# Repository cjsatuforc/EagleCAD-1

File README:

This repository contains the projects I will be using for learning EagleCAD software

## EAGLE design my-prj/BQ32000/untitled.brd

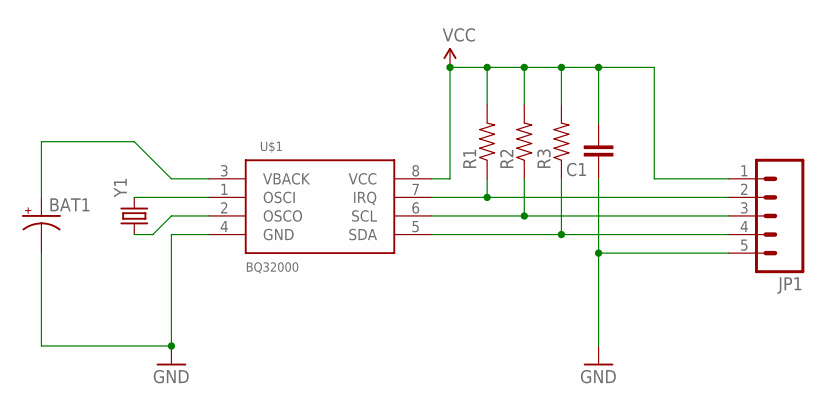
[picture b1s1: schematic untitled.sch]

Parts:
BAT1: CAP_POLPTH3; CPOL-RADIAL-1000UF-63V
C1: CAP0805; 0805
JP1: M05LOCK; 1X05_LOCK
R1, R2, R3: RESISTOR0805-RES; 0805
U$1: BQ32000; SO08
Y1: CRYSTAL32-SMD; CRYSTAL-32KHZ-SMD

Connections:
GND: BAT1.2 (-), C1.1, JP1.5, U$1.4 (GND)
unnamed: BAT1.1 (+), U$1.3 (VBACK)
unnamed: JP1.2, R1.1, U$1.7 (IRQ)
unnamed: JP1.3, R2.1, U$1.6 (SCL)
unnamed: JP1.4, R3.1, U$1.5 (SDA)
unnamed: U$1.1 (OSCI), Y1.X2 (2)
unnamed: U$1.2 (OSCO), Y1.X1 (1)
VCC: C1.2, JP1.1, R1.2, R2.2, R3.2, U$1.8 (VCC)

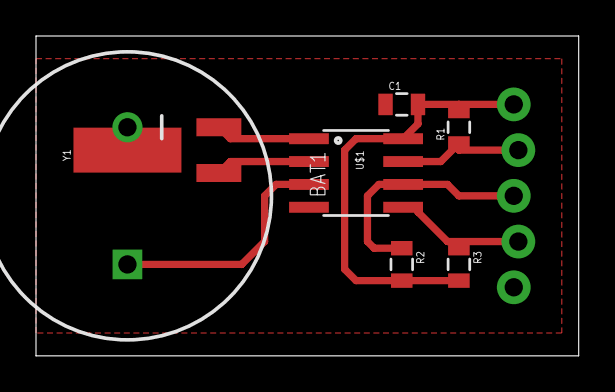
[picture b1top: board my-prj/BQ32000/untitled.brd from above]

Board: 2 copper layers, 30.1 x 17.8 mm, 8 parts (1 on the bottom side), 8 nets.

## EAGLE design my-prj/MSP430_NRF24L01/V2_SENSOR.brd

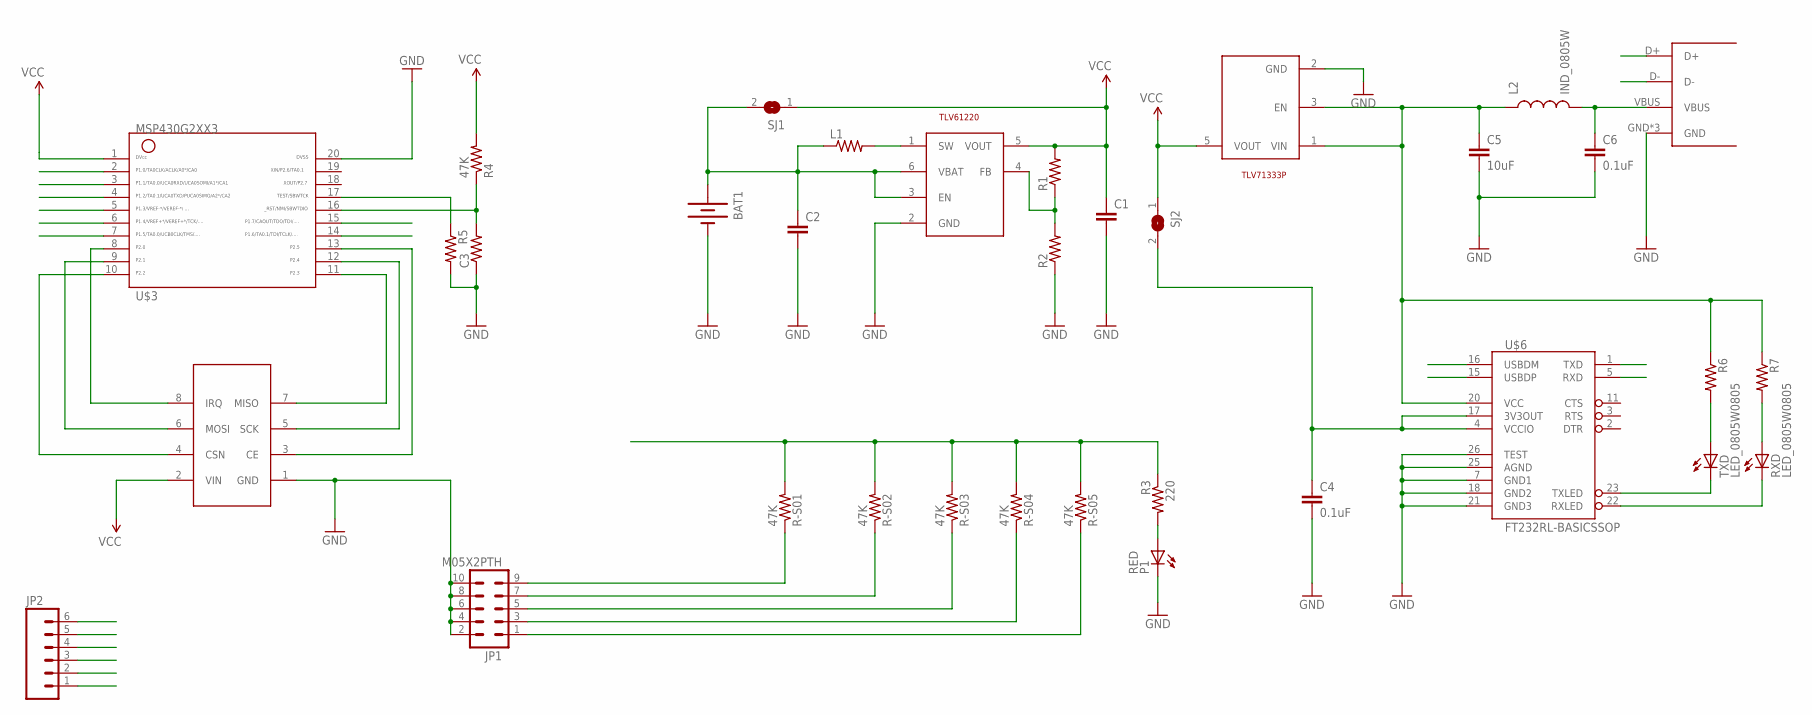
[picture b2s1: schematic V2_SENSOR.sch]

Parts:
BAT1: BATTERY20PTH; BATTCOM_20MM_PTH
C1, C2: CAP_0805W; 0805W
C3: RES_0805W; 0805W
C4, C6: 0.1uF; 0805W
C5: 10uF; 0805W
JP1: M05X2PTH; AVR_ICSP
JP2: M06SIP; 1X06
JP4: USB-A-H
L1: RES_0805W; 0805W
L2: IND_0805W; 0805W
P1: RED; 0805W_LED
R1, R2, R5, R6, R7: RES_0805W; 0805W
R3: 220; 0805W
R4: 47K; 0805W
R-S01, R-S02, R-S03, R-S04, R-S05: 47K; 0805W
RXD: LED_0805W0805; 0805W_LED
SJ1, SJ2: SJ
TXD: LED_0805W0805; 0805W_LED
U1: NRF24L01-4X2
U$2: TLV61220; SOT23-6L
U$3: G2XX3---N20; N20
U$5: TI-TLV71333P; SOT23-5
U$6: FT232RL-BASICSSOP; SSOP28DB

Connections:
5V: C5.1, L2.1, R6.1, R7.1, U$5.1 (VIN), U$5.3 (EN), U$6.20 (VCC)
GND: BAT1.2 (-), C1.2, C2.2, C3.1, C4.2, C5.2, C6.2, JP1.2, JP1.4, JP1.6, JP1.8, JP1.10, JP2.6, JP4.GND, JP4.GND2 (GND), JP4.GND3 (GND), P1.C, R2.1, R5.2, U1.1 (GND), U$2.2 (GND), U$3.20, U$5.2 (GND), U$6.7 (GND1), U$6.18 (GND2), U$6.21 (GND3), U$6.25 (AGND), U$6.26 (TEST)
unnamed: R7.2, RXD.A
unnamed: RXD.C, U$6.22 (RXLED)
unnamed: C6.1, JP4.VBUS, L2.2
unnamed: TXD.C, U$6.23 (TXLED)
unnamed: U1.8 (IRQ), U$3.8
unnamed: BAT1.1 (+), C2.1, L1.1, SJ1.2, U$2.3 (EN), U$2.6 (VBAT)
unnamed: C4.1, SJ2.2, U$6.4 (VCCIO), U$6.17 (3V3OUT)
unnamed: R6.2, TXD.A
unnamed: L1.2, U$2.1 (SW)
unnamed: R1.1, R2.2, U$2.4 (FB)
unnamed: P1.A, R3.2
unnamed: U1.3 (CE), U$3.13
unnamed: U1.5 (SCK), U$3.12
unnamed: U1.7 (MISO), U$3.11
unnamed: U1.6 (MOSI), U$3.9
unnamed: U1.4 (CSN), U$3.10
RESET: C3.2, JP2.3, R4.1, U$3.16
RXD: JP2.5, U$3.3, U$6.1 (TXD)
S1: JP1.9, R-S01.1, U$3.5
S2: JP1.7, R-S02.1, U$3.6
S3: JP1.5, R-S03.1, U$3.7
S4: JP1.3, R-S04.1, U$3.14
S5: JP1.1, R-S05.1, U$3.15
SV: R3.1, R-S01.2, R-S02.2, R-S03.2, R-S04.2, R-S05.2, U$3.2
TEST: JP2.2, R5.1, U$3.17
TXD: JP2.4, U$3.4, U$6.5 (RXD)
USBDM: JP4.D-, U$6.16 (USBDM)
USBDP: JP4.D+, U$6.15 (USBDP)
VCC: C1.1, JP2.1, R1.2, R4.2, SJ1.1, SJ2.1, U1.2 (VIN), U$2.5 (VOUT), U$3.1, U$5.5 (VOUT)

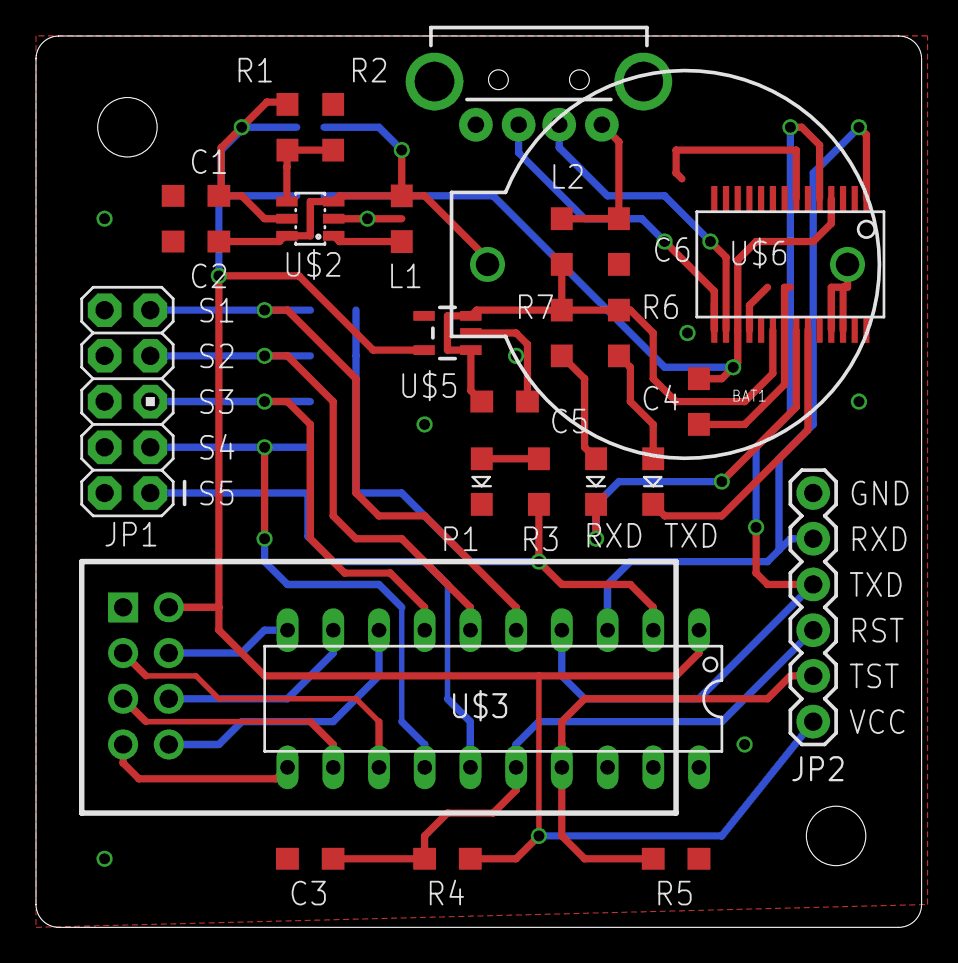
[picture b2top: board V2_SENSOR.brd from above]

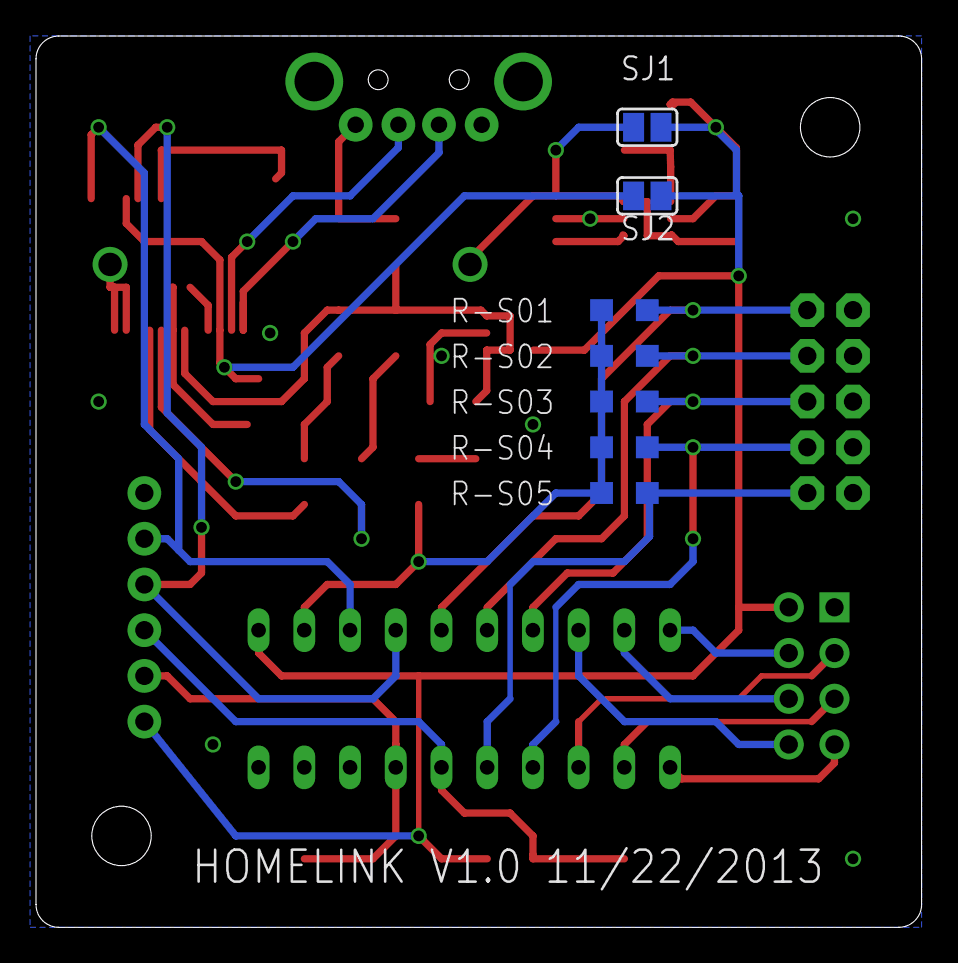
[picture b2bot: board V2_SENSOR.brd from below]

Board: 4 copper layers, 49.2 x 49.5 mm, 36 parts (7 on the bottom side), 31 nets.

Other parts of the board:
U$1, U$4: STAND-OFF

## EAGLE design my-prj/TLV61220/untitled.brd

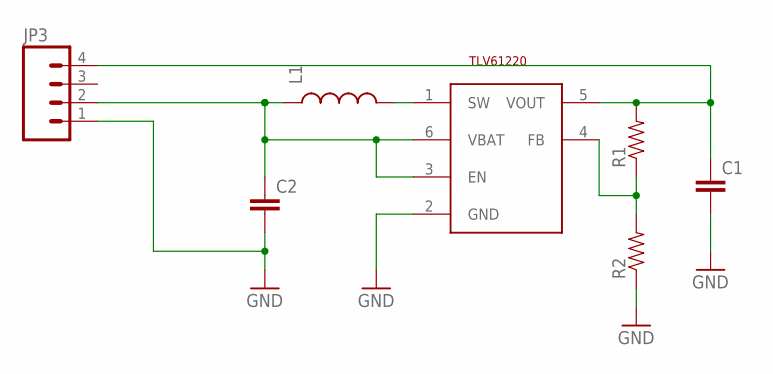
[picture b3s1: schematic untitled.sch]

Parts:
C1, C2: CAP0805; 0805
JP3: M04LOCK; 1X04_LOCK
L1: INDUCTOR0805; 0805
R1, R2: RESISTOR0805-RES; 0805
U$1: TLV61220; SOT23-6L

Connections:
GND: C1.2, C2.2, JP3.1, R2.1, U$1.2 (GND)
unnamed: C1.1, JP3.4, R1.2, U$1.5 (VOUT)
unnamed: L1.2, U$1.1 (SW)
unnamed: R1.1, R2.2, U$1.4 (FB)
VIN: C2.1, JP3.2, L1.1, U$1.3 (EN), U$1.6 (VBAT)

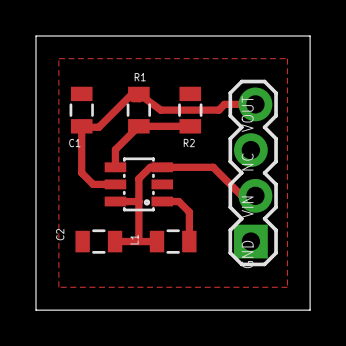
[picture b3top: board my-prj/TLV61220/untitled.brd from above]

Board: 4 copper layers, 15.2 x 15.2 mm, 7 parts (0 on the bottom side), 5 nets.

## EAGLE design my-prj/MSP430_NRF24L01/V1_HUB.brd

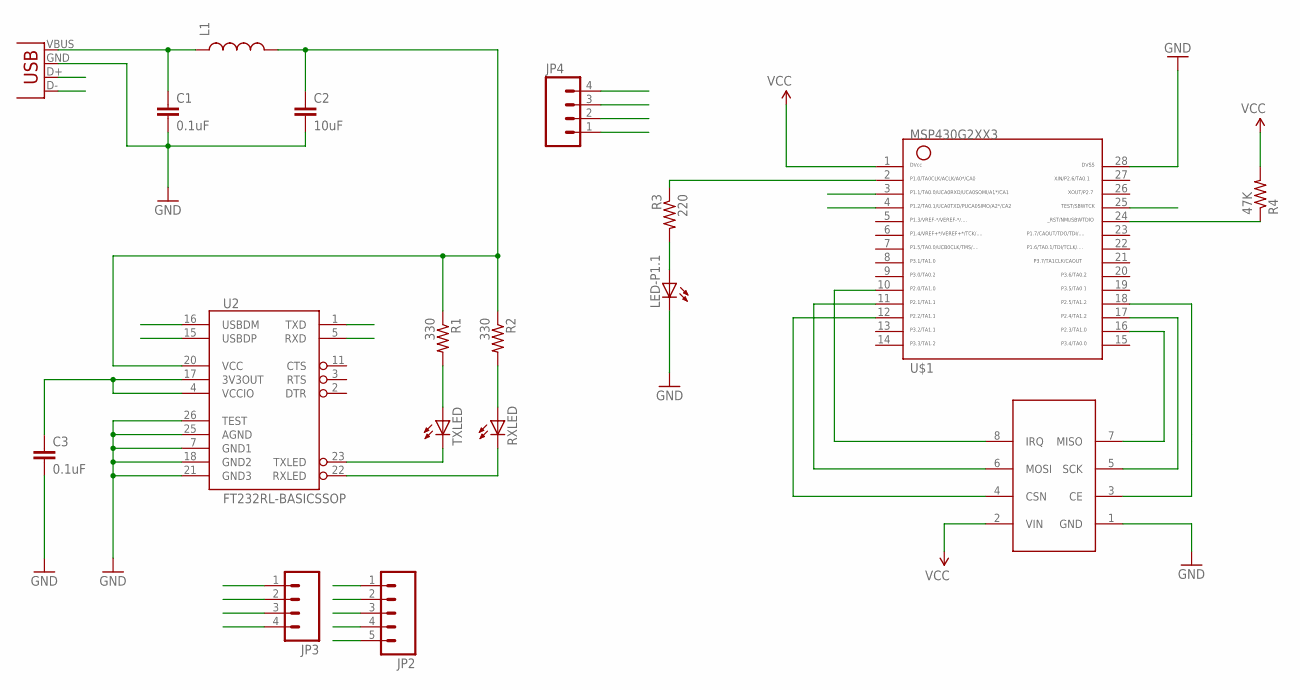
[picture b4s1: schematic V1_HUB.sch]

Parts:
C1, C3: 0.1uF; 0805
C2: 10uF; 0805
JP1: USB-B; USB-A-H
JP2: M05LOCK; 1X05_LOCK
JP3, JP4: M04LOCK; 1X04_LOCK
L1: INDUCTOR0805; 0805
LED-P1.1: LED0805; LED-0805
R1, R2: 330; 0805
R3: 220; 0805
R4: 47K; 0805
RXLED: LED0805; LED-0805
TXLED: LED0805; LED-0805
U1: NRF24L01-4X2
U2: FT232RL-BASICSSOP; SSOP28DB
U$1: MSP430G2553; PW28

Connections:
5V: C2.1, JP2.5, L1.2, R1.1, R2.1, U2.20 (VCC)
GND: C1.2, C2.2, C3.2, JP1.GND (VBUS), JP2.1, JP3.1, JP4.1, LED-P1.1.C, U1.1 (GND), U2.7 (GND1), U2.18 (GND2), U2.21 (GND3), U2.25 (AGND), U2.26 (TEST), U$1.28
unnamed: U1.3 (CE), U$1.18
unnamed: U1.5 (SCK), U$1.17
unnamed: U1.7 (MISO), U$1.16
unnamed: R3.1, U$1.2
unnamed: U1.6 (MOSI), U$1.11
unnamed: U1.4 (CSN), U$1.12
unnamed: U1.8 (IRQ), U$1.10
unnamed: LED-P1.1.A, R3.2
unnamed: R1.2, TXLED.A
unnamed: R2.2, RXLED.A
unnamed: RXLED.C, U2.22 (RXLED)
unnamed: TXLED.C, U2.23 (TXLED)
unnamed: C1.1, JP1.VBUS (GND), L1.1
RESET: JP4.2, R4.1, U$1.24
RX: JP2.3, JP3.3, U2.5 (RXD), U$1.4
TEST: JP4.3, U$1.25
TX: JP2.2, JP3.2, U2.1 (TXD), U$1.3
USBDM: JP1.D- (D+), U2.16 (USBDM)
USBDP: JP1.D+ (D-), U2.15 (USBDP)
VCC: C3.1, JP2.4, JP3.4, JP4.4, R4.2, U1.2 (VIN), U2.4 (VCCIO), U2.17 (3V3OUT), U$1.1

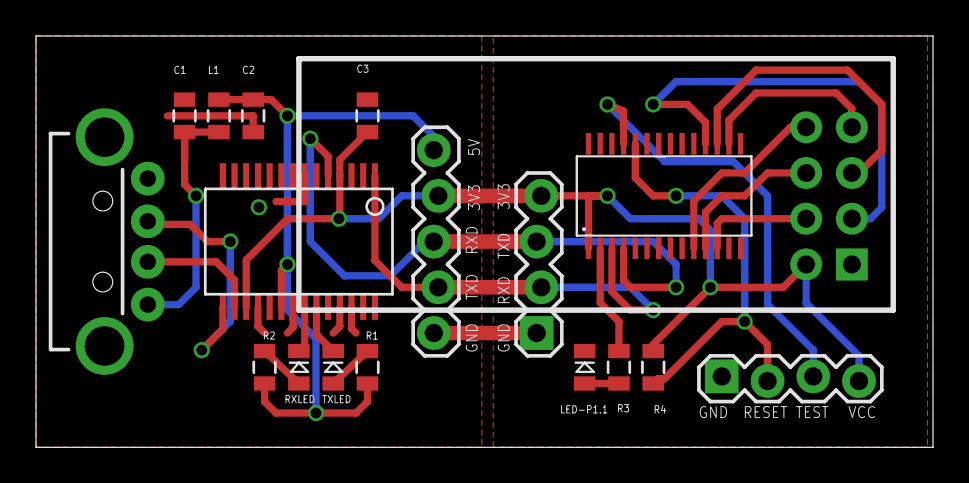
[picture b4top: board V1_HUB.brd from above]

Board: 4 copper layers, 49.8 x 22.9 mm, 18 parts (0 on the bottom side), 22 nets.

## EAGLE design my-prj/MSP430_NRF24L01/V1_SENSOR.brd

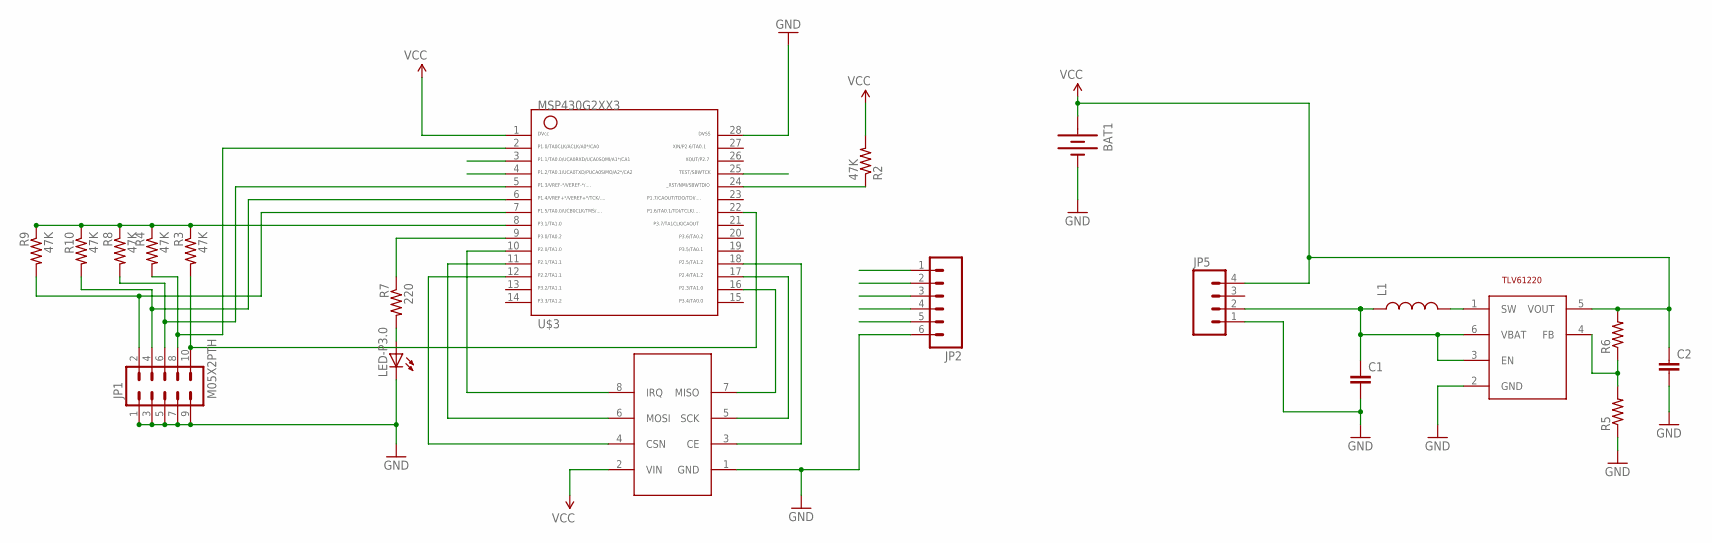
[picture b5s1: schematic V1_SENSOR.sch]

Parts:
BAT1: BATTERY20PTH; BATTCOM_20MM_PTH
C1, C2: CAP0805; 0805
JP1: M05X2PTH; AVR_ICSP
JP2: M06LOCK; 1X06_LOCK
JP5: M04LOCK; 1X04_LOCK
L1: INDUCTOR0805; 0805
LED-P3.0: LED0805; LED-0805
R2, R3, R4, R8, R9, R10: 47K; 0805
R5, R6: RESISTOR0805-RES; 0805
R7: 220; 0805
U2: NRF24L01-4X2
U$2: TLV61220; SOT23-6L
U$3: MSP430G2553; PW28

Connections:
GND: BAT1.2 (-), C1.2, C2.2, JP1.1, JP1.3, JP1.5, JP1.7, JP1.9, JP2.6, JP5.1, LED-P3.0.C, R5.1, U2.1 (GND), U$2.2 (GND), U$3.28
unnamed: R3.1, R4.1, R8.1, R9.1, R10.1, U$3.8
unnamed: L1.2, U$2.1 (SW)
unnamed: R5.2, R6.1, U$2.4 (FB)
unnamed: LED-P3.0.A, R7.2
unnamed: U2.3 (CE), U$3.18
unnamed: U2.5 (SCK), U$3.17
unnamed: U2.7 (MISO), U$3.16
unnamed: U2.6 (MOSI), U$3.11
unnamed: U2.4 (CSN), U$3.12
unnamed: U2.8 (IRQ), U$3.10
unnamed: R7.1, U$3.9
P1.0: JP1.8, R4.2, U$3.2
P1.3: JP1.6, R8.2, U$3.5
P1.4: JP1.4, R10.2, U$3.6
P1.5: JP1.2, R9.2, U$3.7
P1.6: JP1.10, R3.2, U$3.22
RESET: JP2.5, R2.1, U$3.24
RXD: JP2.2, U$3.3
TEST: JP2.4, U$3.25
TXD: JP2.3, U$3.4
VCC: BAT1.1 (+), C2.1, JP2.1, JP5.4, R2.2, R6.2, U2.2 (VIN), U$2.5 (VOUT), U$3.1
VIN: C1.1, JP5.2, L1.1, U$2.3 (EN), U$2.6 (VBAT)

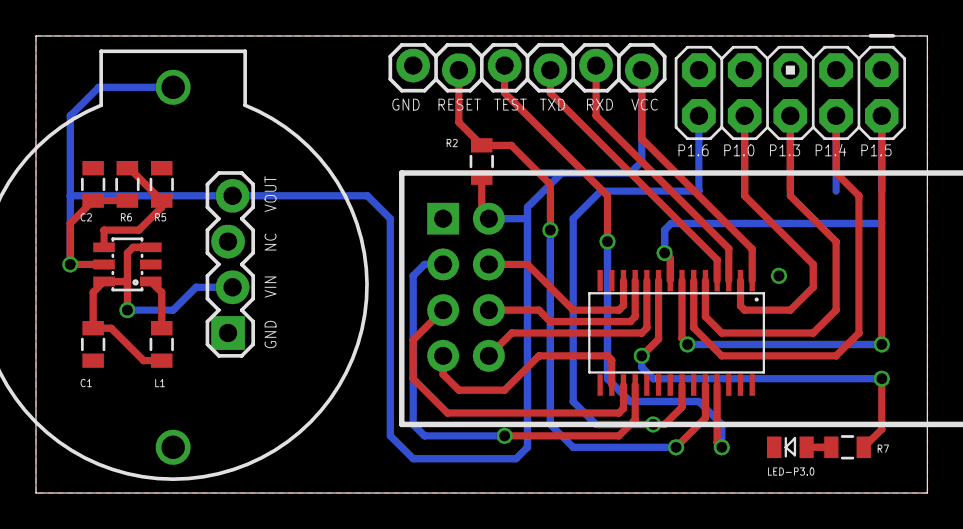
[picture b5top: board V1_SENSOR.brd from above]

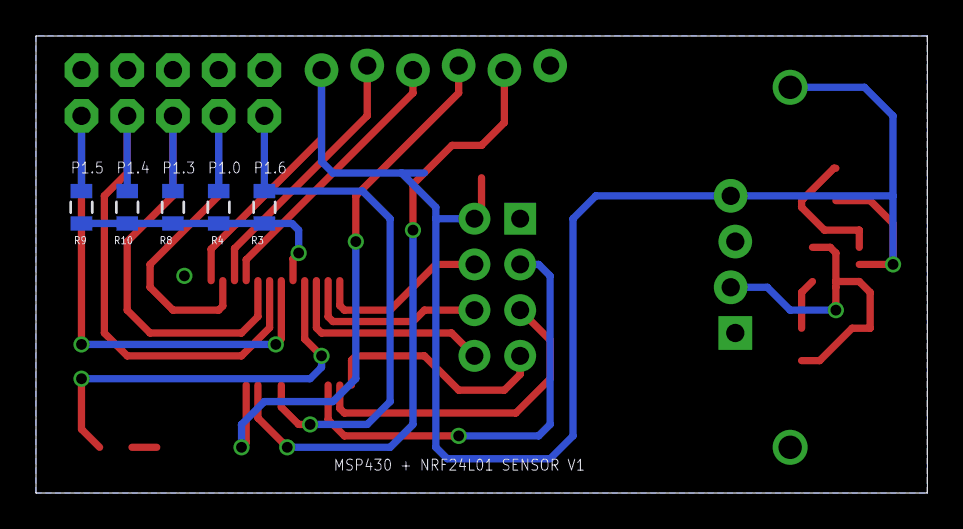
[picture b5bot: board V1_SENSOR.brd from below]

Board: 4 copper layers, 49.5 x 25.4 mm, 20 parts (5 on the bottom side), 23 nets.

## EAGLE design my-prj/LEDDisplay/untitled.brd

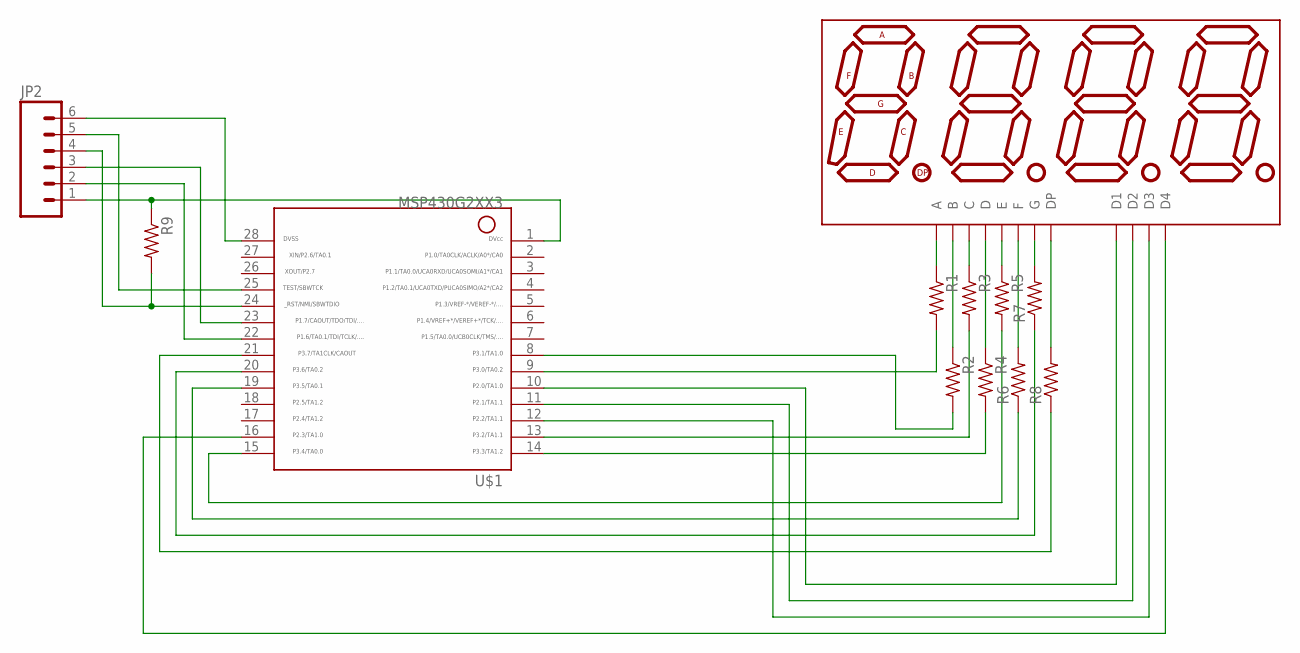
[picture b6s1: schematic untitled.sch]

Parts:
JP2: M06LOCK; 1X06_LOCK
R1, R2, R3, R4, R5, R6, R7, R8, R9: RESISTOR1206; 1206
U$1: G2XX3---PW28; PW28
U$2: 7-SEGMENT-4DIGIT-COUNTERPTH; 7-SEGMENT-4DIGIT-COUNTER

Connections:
unnamed: R1.1, U$2.11 (A)
unnamed: R2.1, U$2.7 (B)
unnamed: R3.1, U$2.4 (C)
unnamed: R4.1, U$2.2 (D)
unnamed: R5.1, U$2.1 (E)
unnamed: JP2.5, U$1.25
unnamed: JP2.4, R9.2, U$1.24
unnamed: JP2.6, U$1.28
unnamed: R8.1, U$1.21
unnamed: JP2.1, R9.1, U$1.1
unnamed: JP2.2, U$1.22
unnamed: R6.2, U$2.10 (F)
unnamed: R7.2, U$2.5 (G)
unnamed: R8.2, U$2.3 (DP)
unnamed: R1.2, U$1.9
unnamed: R2.2, U$1.8
unnamed: R3.2, U$1.13
unnamed: R4.2, U$1.14
unnamed: R5.2, U$1.15
unnamed: R6.1, U$1.19
unnamed: R7.1, U$1.20
unnamed: JP2.3, U$1.23
unnamed: U$1.10, U$2.12 (D1)
unnamed: U$1.11, U$2.9 (D2)
unnamed: U$1.12, U$2.8 (D3)
unnamed: U$1.16, U$2.6 (D4)

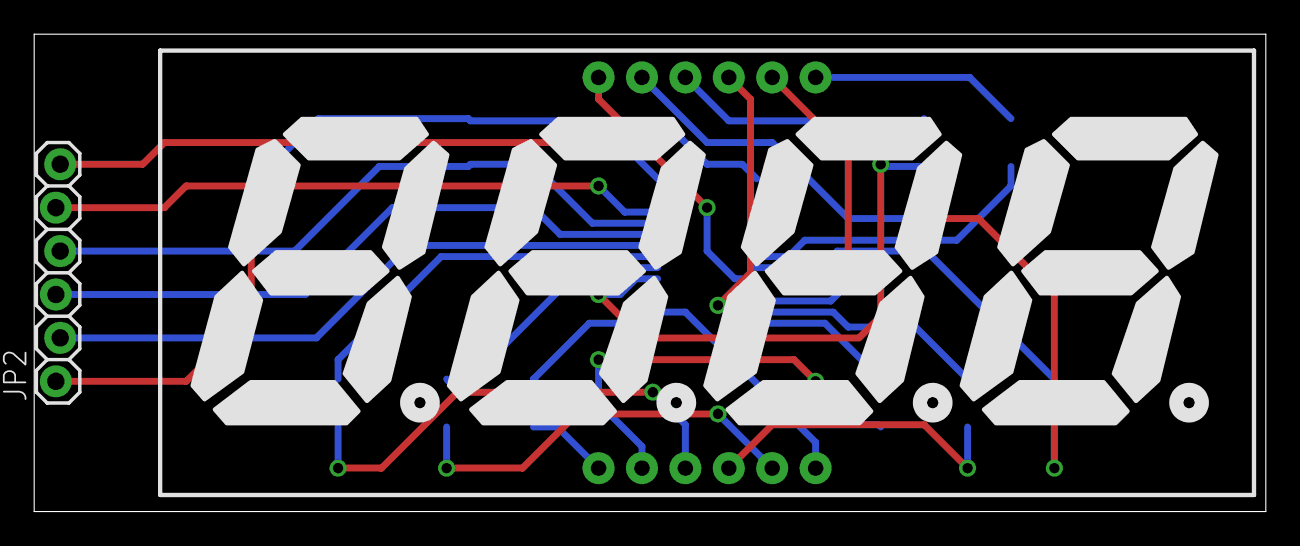
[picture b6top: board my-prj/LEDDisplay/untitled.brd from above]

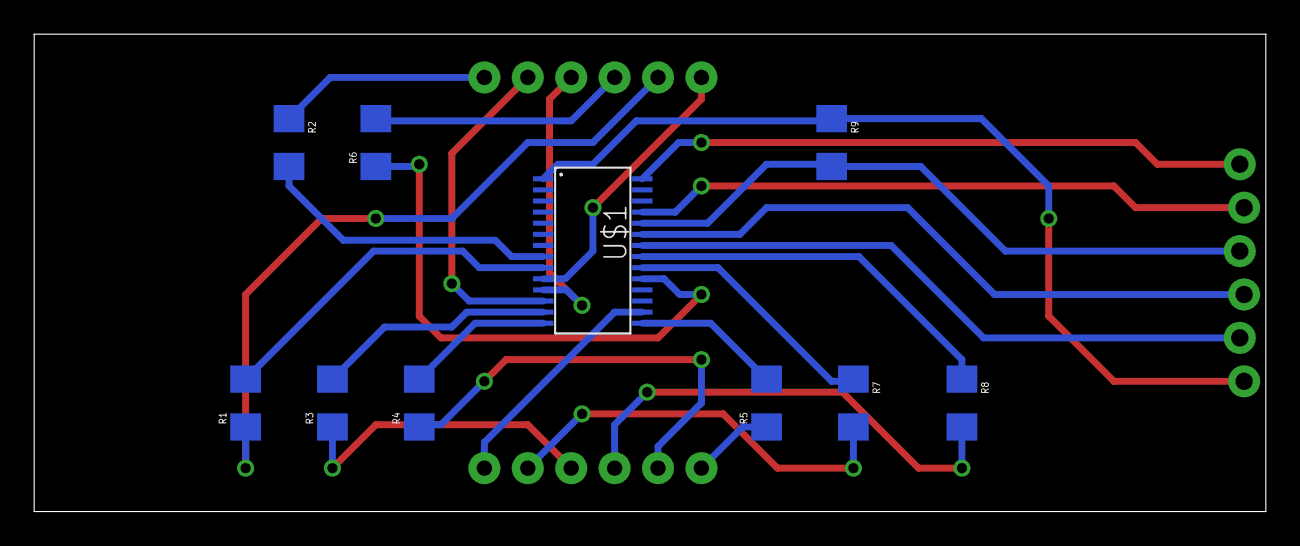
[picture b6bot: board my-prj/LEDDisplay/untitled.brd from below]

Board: 2 copper layers, 72.1 x 27.9 mm, 12 parts (10 on the bottom side), 26 nets.

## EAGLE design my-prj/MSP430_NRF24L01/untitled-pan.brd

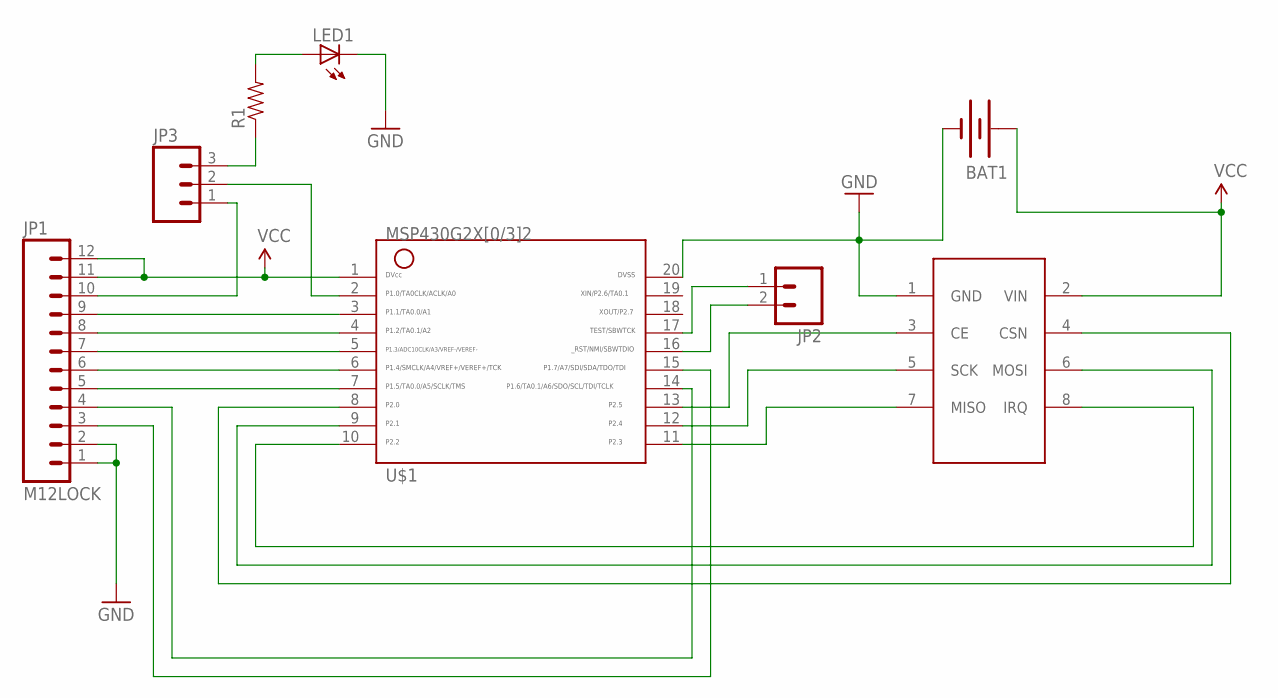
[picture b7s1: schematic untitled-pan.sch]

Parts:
BAT1: BATTERY20PTH; BATTCOM_20MM_PTH
JP1: M12LOCK; 1X12_LOCK
JP2: M02PTH; 1X02
JP3: M03PTH; 1X03
LED1: LED3MM
R1: RESISTORAXIAL-0.3; AXIAL-0.3
U1: NRF24L01-4X2
U$1: G2X[0/3]2---N20; N20

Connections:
GND: BAT1.2 (-), JP1.1, JP1.2, LED1.K (C), U1.1 (GND), U$1.20
unnamed: U1.3 (CE), U$1.13
unnamed: U1.8 (IRQ), U$1.10
unnamed: U1.7 (MISO), U$1.11
unnamed: U1.5 (SCK), U$1.12
unnamed: JP1.4, U$1.14
unnamed: JP1.3, U$1.15
unnamed: JP1.6, U$1.6
unnamed: JP1.7, U$1.5
unnamed: JP1.8, U$1.4
unnamed: JP1.9, U$1.3
unnamed: JP3.2, U$1.2
unnamed: JP1.5, U$1.7
unnamed: JP2.2, U$1.16
unnamed: JP2.1, U$1.17
unnamed: JP3.3, R1.P$1 (1)
unnamed: JP1.10, JP3.1
unnamed: U1.6 (MOSI), U$1.9
unnamed: U1.4 (CSN), U$1.8
unnamed: LED1.A, R1.P$2 (2)
VCC: BAT1.1 (+), JP1.11, JP1.12, U1.2 (VIN), U$1.1

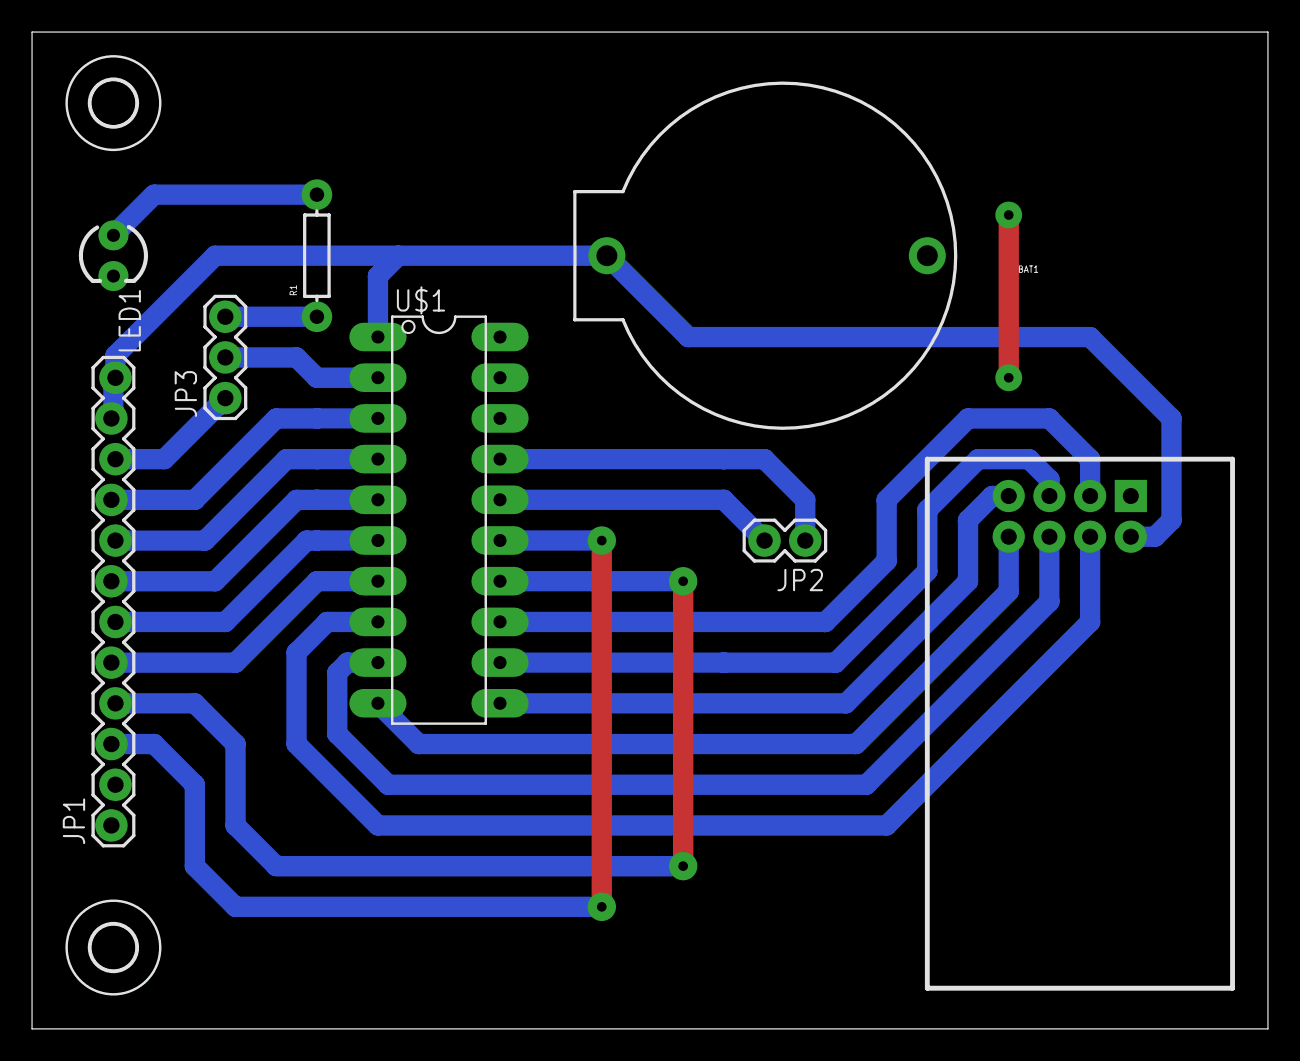
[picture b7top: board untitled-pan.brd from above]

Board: 2 copper layers, 77.1 x 62.2 mm, 10 parts (0 on the bottom side), 21 nets.

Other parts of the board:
U$2, U$5: 2,8

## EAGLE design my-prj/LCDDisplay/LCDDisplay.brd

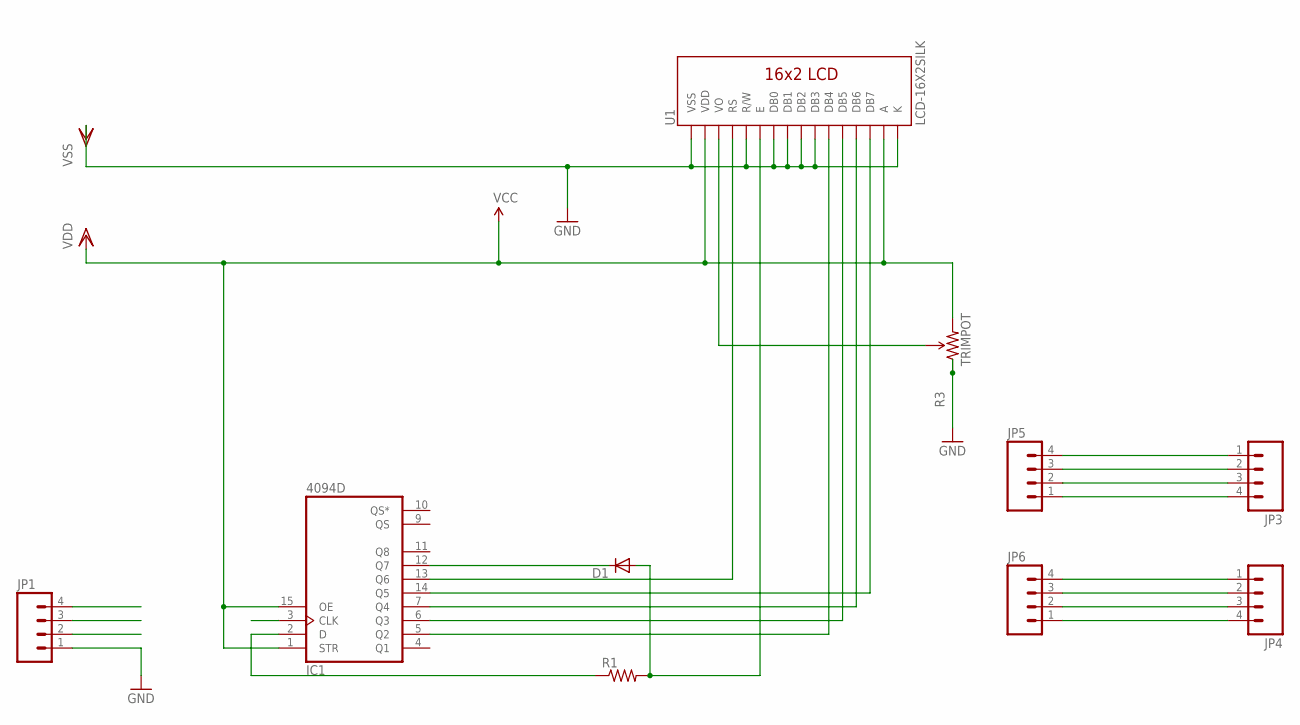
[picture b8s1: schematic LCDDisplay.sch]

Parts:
D1: DIODE1N4148; DIODE-1N4148
IC1: 4094D; SO16
JP1: M04PTH; 1X04
JP3, JP4: M041.27MM; 1X04-1.27MM
JP5, JP6: M04LOCK_LONGPADS; 1X04_LOCK_LONGPADS
R1: RESISTORAXIAL-0.3; AXIAL-0.3
R3: TRIMPOT; 3362U-2
U1: LCD-16X2SILK; LCD-16X2

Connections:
CLK: IC1.3 (CLK), JP1.3
DATA: IC1.2 (D), JP1.4, R1.P$1 (1)
GND: IC1.8 (VSS), JP1.1, R3.1 (CCW), U1.1 (VSS), U1.5 (R/W), U1.7 (DB0), U1.8 (DB1), U1.9 (DB2), U1.10 (DB3), U1.16 (K)
unnamed: IC1.13 (Q6), U1.4 (RS)
unnamed: D1.A, R1.P$2 (2), U1.6 (E)
unnamed: R3.2 (WIPER), U1.3 (VO)
unnamed: D1.C, IC1.12 (Q7)
unnamed: JP3.1, JP5.4
unnamed: IC1.5 (Q2), U1.11 (DB4)
unnamed: IC1.6 (Q3), U1.12 (DB5)
unnamed: JP3.2, JP5.3
unnamed: IC1.7 (Q4), U1.13 (DB6)
unnamed: IC1.14 (Q5), U1.14 (DB7)
unnamed: JP3.3, JP5.2
unnamed: JP3.4, JP5.1
unnamed: JP4.1, JP6.4
unnamed: JP4.2, JP6.3
unnamed: JP4.3, JP6.2
unnamed: JP4.4, JP6.1
VDD: IC1.1 (STR), IC1.15 (OE), IC1.16 (VDD), JP1.2, R3.3 (CW), U1.2 (VDD), U1.15 (A)

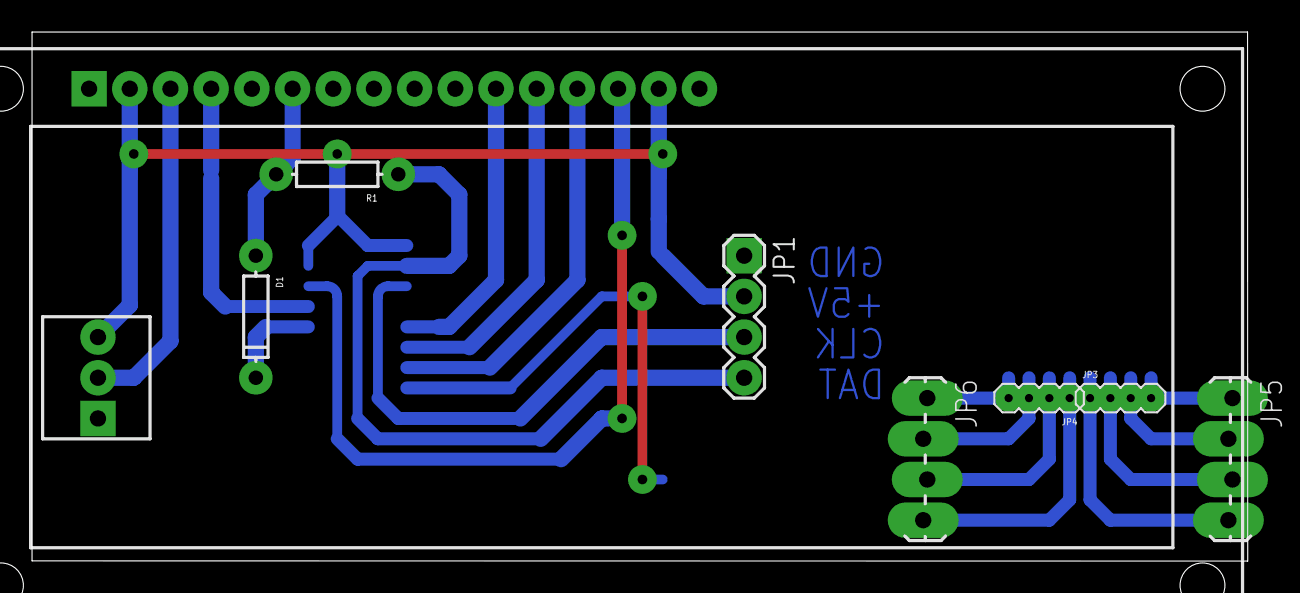
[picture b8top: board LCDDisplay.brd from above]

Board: 2 copper layers, 75.9 x 33.0 mm, 10 parts (1 on the bottom side), 20 nets.

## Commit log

2013-01-22 Adding SparkFun libraries
2013-01-22 Updating FT232 breakout project
2013-01-24 Adding 16x2 LCD display parallel to serial adapter
2013-02-04 Updating directory structure
2013-04-23 NRF24L01 MSP430 experiment board
2013-07-07 deleted: my-lbr/untitled.lbr deleted: my-prj/FT232-Breakout/FT232-Breakout.brd deleted: my-prj/FT232-Breakout/FT232-Breakout.sch deleted: my-prj/FT232-Breakout/eagle.epf deleted: my-prj/LCDDisplay/LC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
2013-12-09 adding new files

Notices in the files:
parts and their libraries:
SparkFun-Passives: Licensing: CC v3.0 Share-Alike You are welcome to use this library for commercial purposes.
